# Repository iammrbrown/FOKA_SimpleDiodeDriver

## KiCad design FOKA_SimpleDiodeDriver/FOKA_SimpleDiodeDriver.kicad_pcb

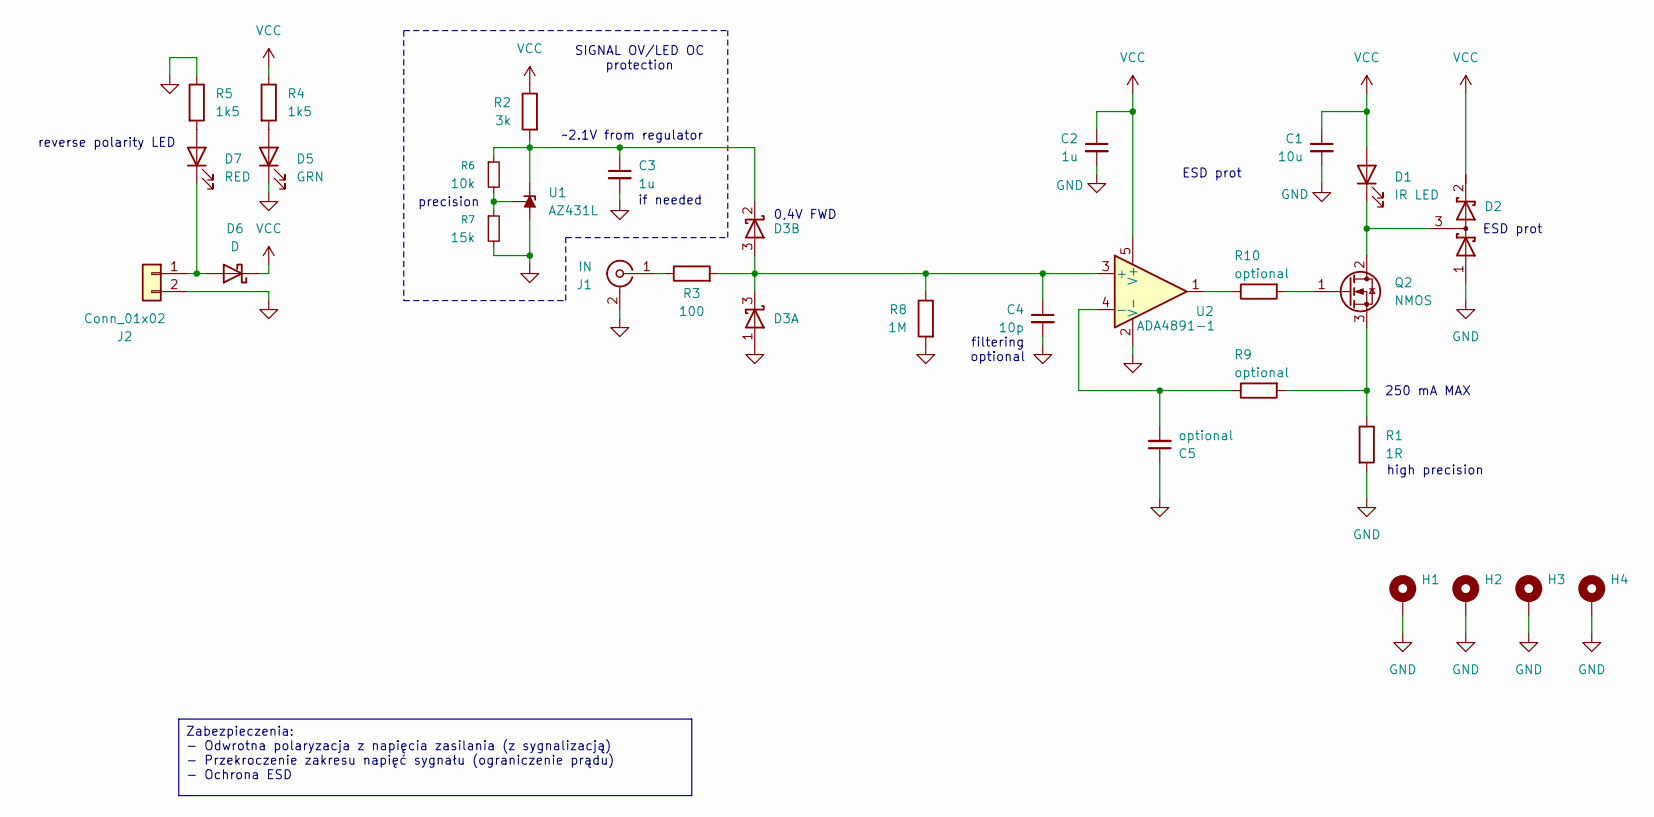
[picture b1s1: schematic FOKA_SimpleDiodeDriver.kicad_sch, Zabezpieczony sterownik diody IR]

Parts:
C1: 10u; C_0805_2012Metric_Pad1.18x1.45mm_HandSolder
C2, C3: 1u; C_0603_1608Metric_Pad1.08x0.95mm_HandSolder
C4: 10p; C_0603_1608Metric_Pad1.08x0.95mm_HandSolder
C5: optional; C_0402_1005Metric
D1: IR LED; TO-18-2_Window
D2: D_Schottky_Dual_Series_AKC; SOT-23-3
D3: D_Schottky_Dual_Series_AKC_Split; SOT-23-3
D5: GRN; LED_0805_2012Metric_Pad1.15x1.40mm_HandSolder
D6: D; D_SOD-123F
D7: RED; LED_0805_2012Metric_Pad1.15x1.40mm_HandSolder
H1, H2, H3, H4: MountingHole_Pad; MountingHole_3.2mm_M3_Pad_Via
J1: IN; SMA_Amphenol_132289_EdgeMount
J2: Conn_01x02; 691313510002
Q2: NMOS; SOT-89-3
R1: 1R; R_1206_3216Metric_Pad1.30x1.75mm_HandSolder
R2: 3k; R_0603_1608Metric_Pad0.98x0.95mm_HandSolder
R3: 100; R_0603_1608Metric_Pad0.98x0.95mm_HandSolder
R4, R5: 1k5; R_0603_1608Metric_Pad0.98x0.95mm_HandSolder
R6: 10k; R_0603_1608Metric_Pad0.98x0.95mm_HandSolder
R7: 15k; R_0603_1608Metric_Pad0.98x0.95mm_HandSolder
R8: 1M; R_0603_1608Metric_Pad0.98x0.95mm_HandSolder
R9, R10: optional; C_0402_1005Metric
U1: AZ431L; SOT-23-3
U2: ADA4891-1; SOT-23-5_HandSoldering

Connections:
GND: C1.2, C2.2, C3.2, C4.2, C5.1, D2.1 (A), D3.1 (A), D5.1 (K), H1.1, H2.1, H3.1, H4.1, J1.2 (Ext), J2.2, R1.2, R5.1, R7.2, R8.2, U1.3 (A), U2.2 (V-)
unnamed: D1.1 (K), D2.3 (common), Q2.2 (D)
unnamed: C4.1, D3.3 (K), R3.2, R8.1, U2.3 (+)
unnamed: D5.2 (A), R4.2
unnamed: D6.2 (A), D7.1 (K), J2.1
unnamed: D7.2 (A), R5.2
unnamed: J1.1 (In), R3.1
unnamed: Q2.1 (G), R10.2
unnamed: Q2.3 (S), R1.1, R9.2
unnamed: R10.1, U2.1
unnamed: C3.1, D3.2 (K), R2.2, R6.1, U1.2 (K)
unnamed: R6.2, R7.1, U1.1 (REF)
unnamed: C5.2, R9.1, U2.4 (-)
VCC: C1.1, C2.1, D1.2 (A), D2.2 (K), D6.1 (K), R2.1, R4.1, U2.5 (V+)

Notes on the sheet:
high precision
0,4V FWD
filtering optional
reverse polarity LED
ESD prot
SIGNAL OV/LED OC protection
~2.1V from regulator
250 mA MAX
precision
if needed
Zabezpieczenia: - Odwrotna polaryzacja z napięcia zasilania (z sygnalizacją) - Przekroczenie zakresu napięć sygnału (ograniczenie prądu) - Ochrona ESD

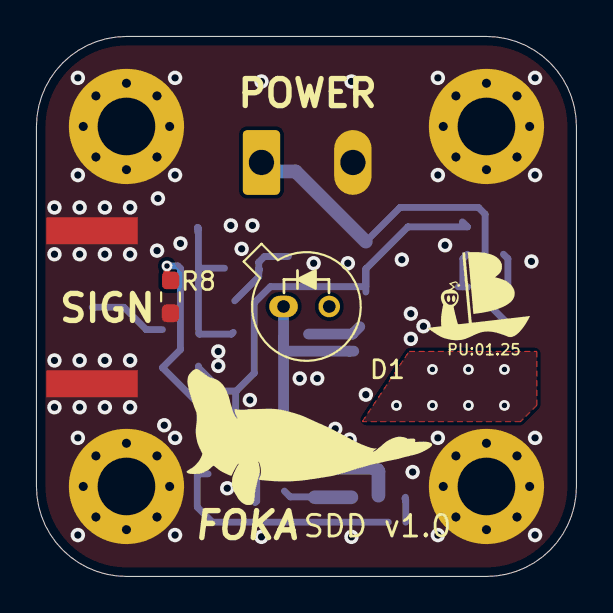
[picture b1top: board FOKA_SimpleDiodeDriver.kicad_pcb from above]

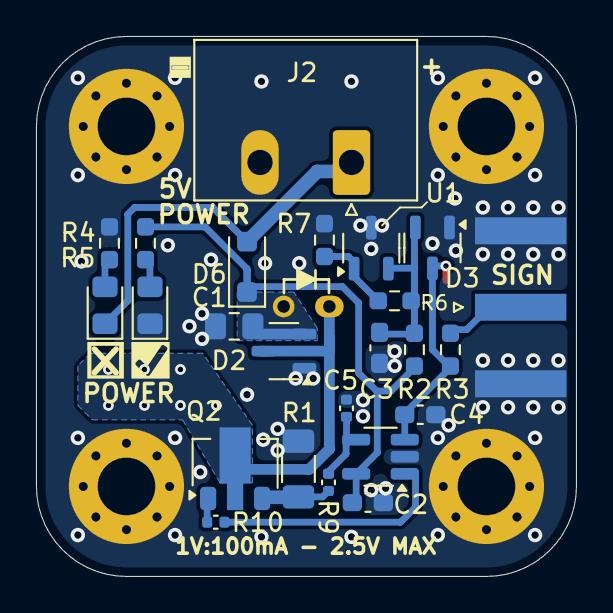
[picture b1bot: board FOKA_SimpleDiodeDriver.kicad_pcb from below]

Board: 2 copper layers, 30.0 x 30.0 mm, 30 parts (24 on the bottom side), 14 nets.

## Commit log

2025-02-02 INIT: version 0.1
2025-04-14 v0.9
    awaiting pre-production review
2025-07-01 minor updates
2025-07-02 recommended changes
    voltage reference as OC prot.
    layout changes
    made vias bigger
2025-07-02 BJT -> NMOS
2025-10-14 Humpback update drop
2025-10-29 Final?
2025-10-29 RezystorDoBramki
